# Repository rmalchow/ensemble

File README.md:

# ensemble has moved — it's now called Ondaire

This project was renamed. "Ensemble" is now **Ondaire**, self-hosted synchronized multiroom audio.

- New GitLab repo: https://gitlab.rand0m.me/share/ondaire
- New GitHub repo: https://github.com/rmalchow/ondaire

Please update your bookmarks, clones, and CI references — this repository is a placeholder only and receives no further updates.

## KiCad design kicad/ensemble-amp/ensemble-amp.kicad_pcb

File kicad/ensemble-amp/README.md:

# ensemble-amp — ESP32-S3 I2S Audio Amplifier

USB-C PD (20 V) → buck/LDO rails → ESP32-S3 → I2S → PCM5102A DAC → TPA3118D2 Class-D amp → stereo speakers.

**Single USB-C connector does everything**: PD negotiation runs on the CC wires while
USB 2.0 data (native ESP32-S3 USB, flashing/debug) runs on D+/D− — both at the same time.

Generated KiCad 10 project: schematic is **ERC-clean**, PCB has all footprints
**placed in functional blocks with full net assignment** — routing is left to you
(DRC shows only the expected unrouted ratsnest + silkscreen cosmetics).

## Architecture

```
USB-C ── CC1/CC2 ── HUSB238A PD sink (GPIO mode: 19.1k VSET=20V, 21k ISET=3A)
  │ VBUS ── SMAJ24A TVS ──── Q1 PMOS load switch (GATE-driven, soft start) ── VAMP rail (5…20V)
  │                                                                            ├─ TPA3118D2 PVCC/AVCC ── LC filters ── SPK L/R
  │                                                                            ├─ AP63205 buck → 5V ── AP2112K → 3.3V ── FB1 → 3V3A
  │                                                                            └─ 100k/10k divider → ESP32 ADC (IO7, rail monitor)
  └ D+/D− ── USBLC6 ESD ── ESP32-S3 native USB (flash/debug, works on any port)
ESP32-S3 ── I2S ── PCM5102A ── RC + AC coupling ── amp inputs
   └── I2C OLED · EC11 encoder · LEDs · UART header · amp control · PD_FAULT (IO14)
```

### How the PD negotiation behaves

The HUSB238A requests 20 V/3 A and walks the charger's PDO list from the top, taking the
first profile that satisfies ≥3 A — so the rail adapts to whatever you plug in:

| Charger | Rail (VAMP) | Approx. max audio power |
|---|---|---|
| 60 W+ PD | 20 V | ~2×25 W/8Ω, ~2×45 W/4Ω |
| 45 W PD | 15 V | ~2×14 W/8Ω, ~2×28 W/4Ω |
| 27–30 W PD | 9–12 V | ~2×5–9 W/8Ω |
| Plain USB port | 5 V | logic only — flashing/debug |

Firmware reads the actual rail through the 100k/10k divider on **IO7** (ADC1) — display
it on the OLED. **IO14 (PD_FAULT)** goes high if the charger can't cover the request or a
fault occurs. The amp's SDZ stays low until firmware decides the rail is adequate.

## Key design choices

- **USB-PD GPIO mode, not I2C**: in GPIO mode the HUSB238A's SDA/SCL pins permanently
  become the VSET/ISET analog straps, and sharing them with the ESP32 I2C bus would corrupt
  the strap reading at plug-in. Status is read via ADC + FAULT pin instead — robust, zero
  protocol risk. (ADDR/ORIENT floats = GPIO mode, per datasheet Table 6.)
- **Load switch**: HUSB238A GATE (open drain) drives the SUD45P03 PMOS; 100k gate pull-up,
  BZT52C10 zener clamps Vgs to −10 V (rail can be 20 V, FET Vgs(max) is ±20 V), 10 nF gives
  soft start. This matches the datasheet's GPIO-mode typical application (Fig. 4) one-to-one.
  Dead-battery attach is supported and the typical app has no other power path, so the
  switch closes at plain 5 V — the board boots when plugged into a computer. The chip's own
  OVP (120 % of requested voltage) opens the PMOS on overvoltage as a bonus protection layer.
  (Datasheet is marked *Preliminary*; GATE turn-on timing is an OTP option — verify on first
  article that VAMP comes up on a non-PD port.)
- **AP2112K-3.3 LDO** (250 mV dropout) instead of AMS1117 so the 3.3 V rail stays solid even
  in the 5 V-fallback case (buck output ≈4.7 V).
- **35 V bulk capacitors** (470 µF ×4) for the 20 V rail.
- **TPA3118D2 instead of TPA3116D2**: identical die and pinout (TI SLOS708G), but the
  thermal pad faces *down* — cooled by the PCB through the thermal-via array, no
  bolt-on heatsink. At 12 V both parts are supply-limited to the same output
  (~2×15 W @ 8 Ω, ~2×25 W @ 4 Ω). The amp symbol is in the project-local
  `ensemble.kicad_sym` library.
- **Gain**: 20 dB BTL master (R13 = 5.6 kΩ from GAIN/SLV to GND, datasheet Table).
  PCM5102A full scale is 2.1 Vrms → drives the amp to full 12 V output with margin.
- **MODSEL** tied low → classic BD modulation (matches the 10 µH + 680 nF output filter).
  AM0–AM2 low → default 400 kHz switching.
- **PLIMIT** tied to GVDD → no power limiting. Add a divider later if you want to cap output.
- **SDZ / MUTE** driven from GPIO through 100 kΩ series resistors (datasheet slew-rate
  requirement) with 100 kΩ pulldowns → amp stays off/un-muted-low until firmware says so.
- **PCM5102A** hardware-config mode: SCK grounded (internal PLL from BCK), FMT=I2S,
  FLT=normal, DEMP=off. XSMT has a 10 kΩ pulldown → DAC stays soft-muted until GPIO13 goes high.
- **Audio path**: OUT → 100 Ω + 2.2 nF RC (TPA3118 input sees clean HF) → 1 µF AC coupling →
  INP; INN AC-coupled to ground per channel (single-ended use of the differential input).
- **3V3A**: ferrite-isolated analog rail for PCM5102A AVDD/CPVDD.
- **USB data**: USBLC6 ESD protection on D+/D− (its VBUS clamp pin references the internal
  5 V rail, since connector VBUS may be 20 V). CC pulldowns are inside the HUSB238A.

## GPIO map (ESP32-S3)

| Function | GPIO | | Function | GPIO |
|---|---|---|---|---|
| I2S BCLK | IO15 | | Encoder A / B / SW | IO4 / IO5 / IO6 |
| I2S LRCK | IO16 | | Amp SDZ (high = on) | IO10 |
| I2S DOUT | IO17 | | Amp MUTE (high = mute) | IO11 |
| I2C SDA (OLED) | IO8 | | Amp FAULTZ (in, low = fault) | IO12 |
| I2C SCL (OLED) | IO9 | | DAC XSMT (high = unmute) | IO13 |
| Status LED 1 / 2 | IO47 / IO48 | | UART TX / RX (J3) | TXD0 / RXD0 |
| Spare on J3 | IO1, IO2 | | Boot / Reset buttons | IO0 / EN |
| VAMP sense (ADC1, 100k/10k) | IO7 | | PD fault (in, high = fault) | IO14 |

Power-up sequence in firmware: configure I2S → XSMT high → SDZ high → MUTE low.

## Routing guidance (the part left for you)

1. **Ground**: pour the B.Cu GND zone first (both zone outlines are already in the file,
   unfilled). Keep DAC/analog ground returns away from the amp's switching return paths.
2. **Amp**: PVCC decoupling (C36–C40) right at pins 18/19/31/32 with short, wide traces;
   bootstrap caps (C43–C46) directly at their pins; OUTx → L → film cap → terminal with
   ≥1.5 mm traces (AmpOutput net class is pre-set). Stitch the thermal-via pad to both GND planes.
3. **Buck**: keep the SW5V node (U1 pin SW → L1) tiny; input cap C4 hugging VIN/GND pins.
4. **USB**: route IO19/IO20 → USBLC6 → connector as a ~90 Ω differential pair (short here,
   so geometry is forgiving).
5. **Antenna**: the keep-out zone under the ESP32 antenna (both layers) is already placed —
   don't route or pour under it. Module antenna faces the bottom board edge.

## DRC notes (intentional)

- `unconnected_items`: the board ships unrouted by design.
- USB-C shield pads sit 0.15 mm from the board edge (connector overhangs); the project
  edge-clearance rule is set to 0.1 mm accordingly.
- Min through-hole is set to 0.2 mm for the ESP32 footprint's thermal vias.
- Silkscreen overlaps are cosmetic; nudge refdes during routing.

## Bring-up checklist

1. Populate the PD front end (U7, Q1 + gate parts, TVS) + buck/LDO. Plug into a plain USB
   port first: VAMP ≈ 5 V, +5 V/+3V3 up. Then a PD charger: VAMP should step to 20 V (or 15 V
   on a 45 W charger) about a second after attach.
2. Populate ESP32. Flash over USB-C (hold BOOT, tap RESET). Verify 3V3 ≥3.2 V during Wi-Fi TX.
3. Populate DAC; play I2S tone, scope OUTL/OUTR (2.1 Vrms max, 3 V DC bias before caps is normal **inside** the DAC — the outputs themselves are ground-centered).
4. Populate amp; SDZ low at first power, then enable with a small speaker / dummy load.

## Files

- `ensemble-amp.kicad_pro` / `.kicad_sch` / `.kicad_pcb` — open with KiCad ≥ 9
- `ensemble.kicad_sym` + `sym-lib-table` — project-local TPA3118D2 symbol
- `ensemble-amp-bom.csv` — grouped BOM (42 lines, ~85 components)
- `../generator/` — Python generators (single source of truth in `design.py` +
  `pcb_positions.py`; regenerate with `python3 gen_sch.py ../ensemble-amp/ensemble-amp.kicad_sch`
  and `python3 gen_pcb.py ../ensemble-amp/ensemble-amp.kicad_pcb`)

> ⚠ Generated design — review schematic and datasheet-critical values before ordering boards.

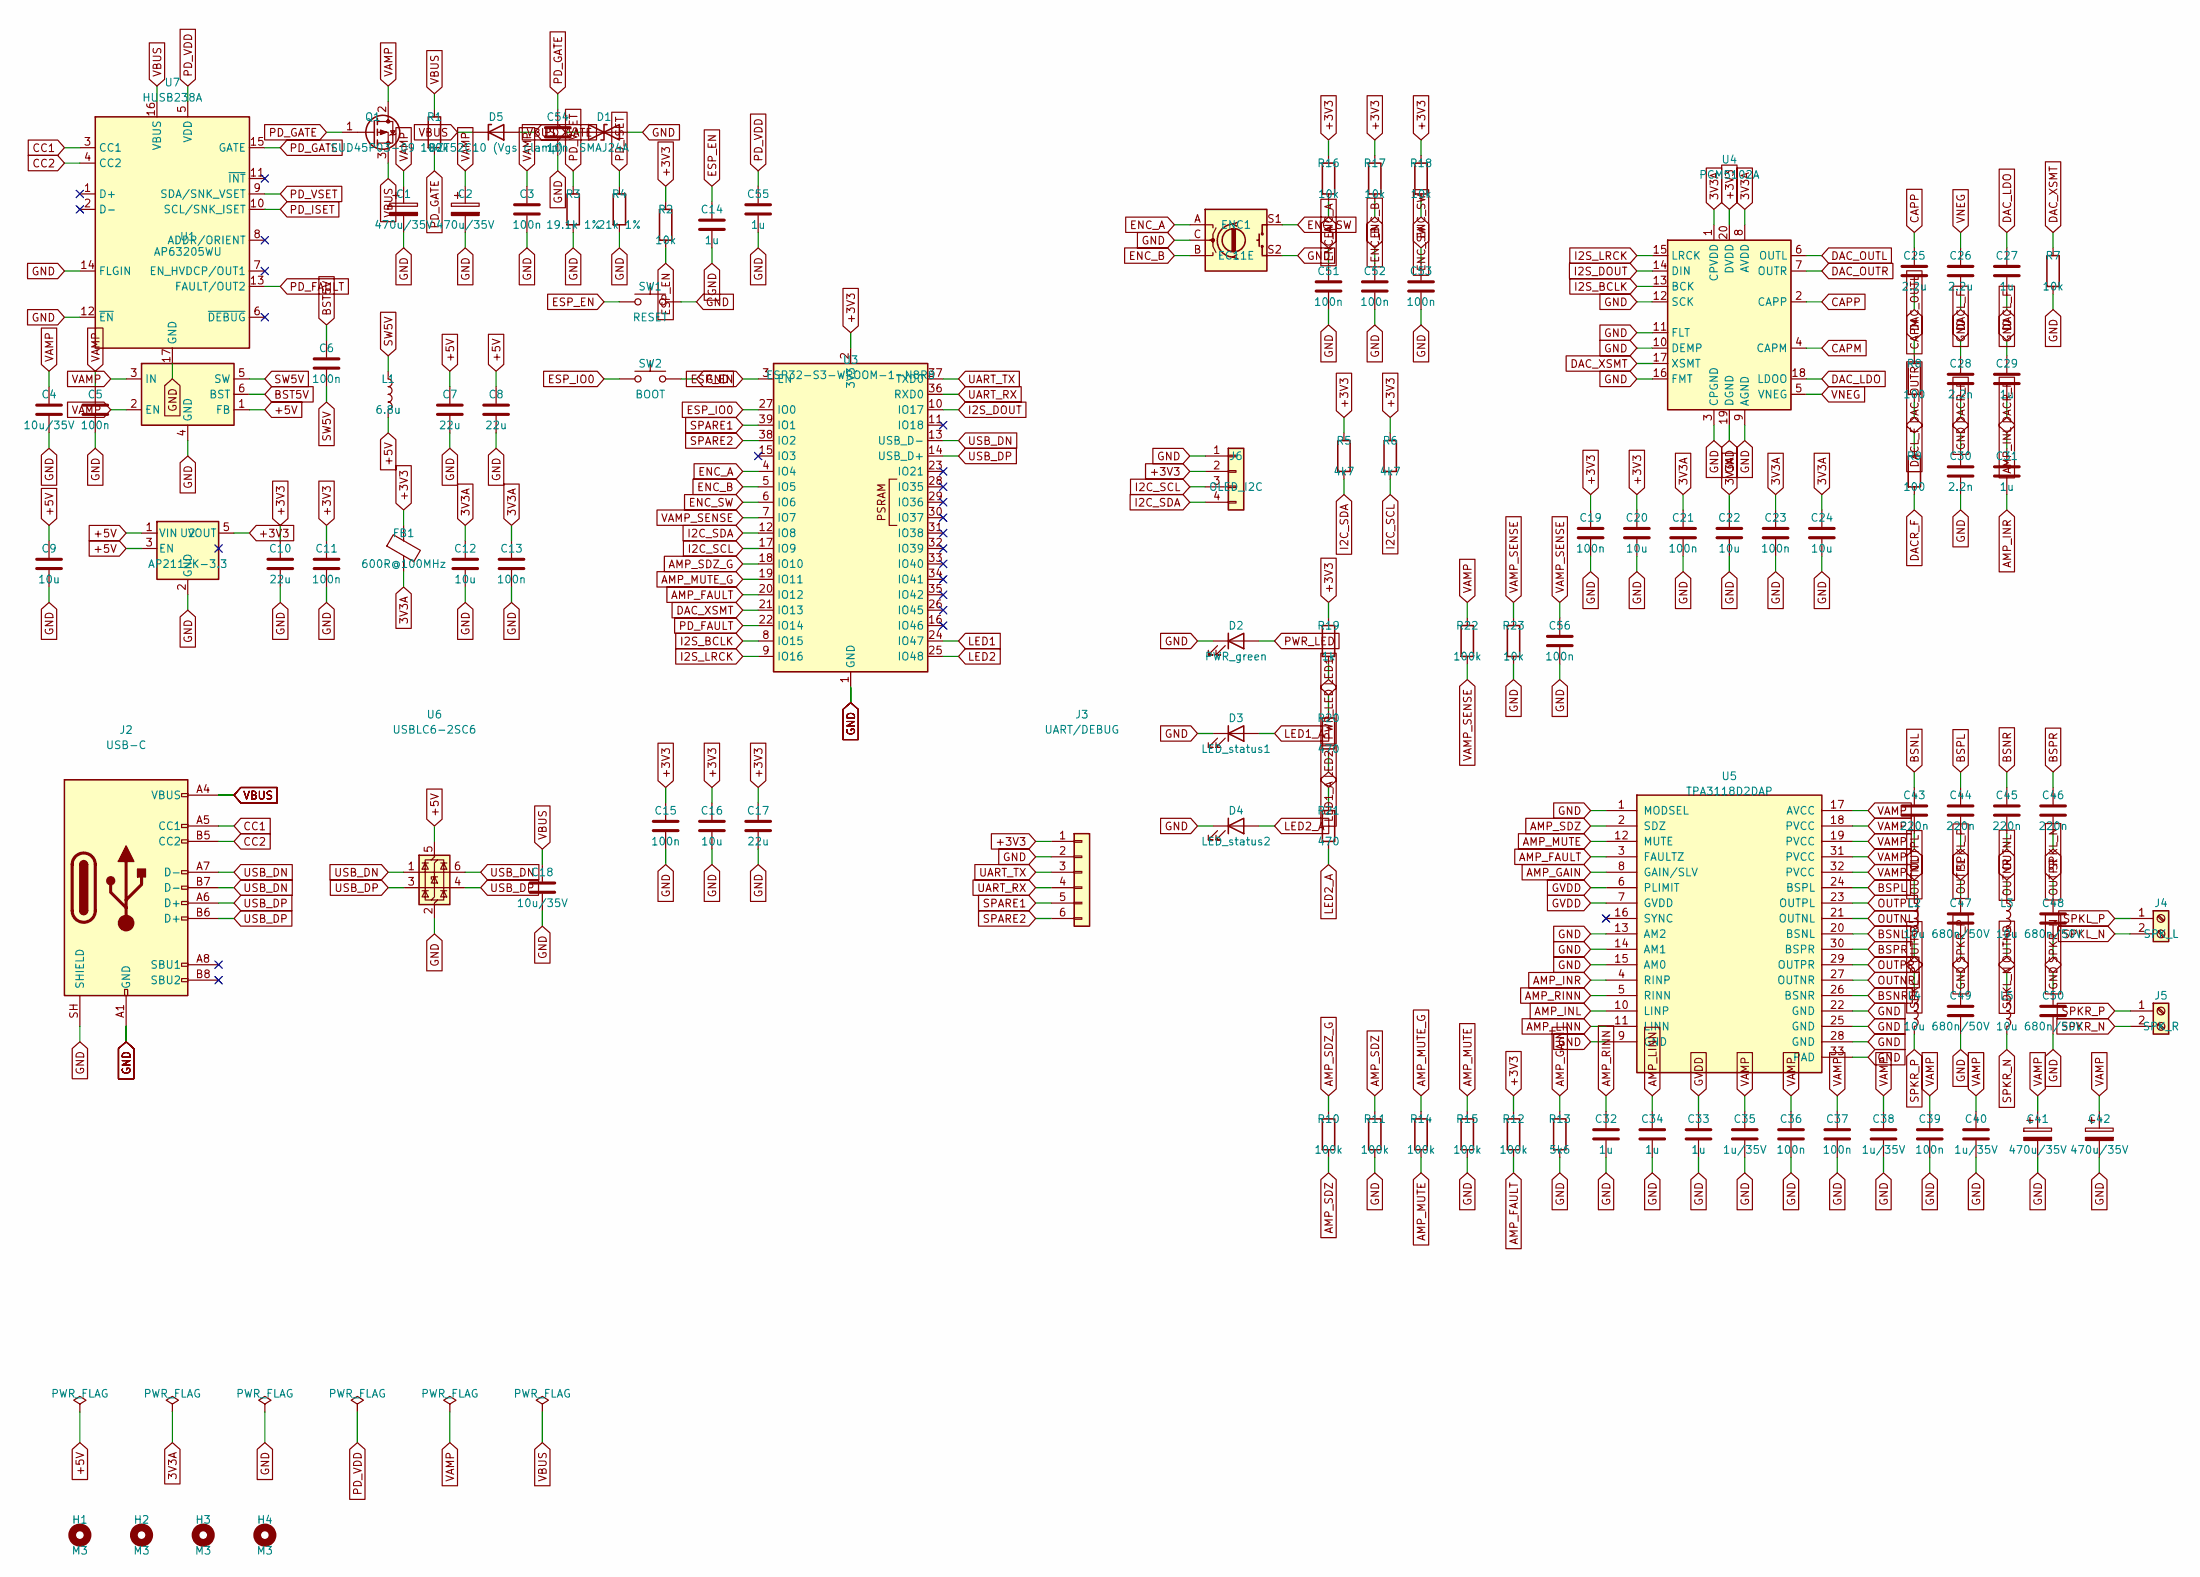
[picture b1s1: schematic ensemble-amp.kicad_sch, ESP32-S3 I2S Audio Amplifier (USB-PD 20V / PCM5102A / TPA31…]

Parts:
C1, C2, C41, C42: 470u/35V; CP_Radial_D12.5mm_P5.00mm
C3, C5, C6, C11, C13, C15, C19, C21, C23, C36, C37, C39, C51, C52, C53, C56: 100n; C_0603_1608Metric
C4, C18: 10u/35V; C_1210_3225Metric
C7, C8, C10, C17: 22u; C_0805_2012Metric
C9, C12, C16, C20, C22, C24: 10u; C_0805_2012Metric
C14, C27, C29, C31, C32, C33, C34, C55: 1u; C_0603_1608Metric
C25, C26: 2.2u; C_0805_2012Metric
C28, C30: 2.2n; C_0603_1608Metric
C35, C38, C40: 1u/35V; C_0603_1608Metric
C43, C44, C45, C46: 220n; C_0603_1608Metric
C47, C48, C49, C50: 680n/50V; C_1210_3225Metric
C54: 10n; C_0603_1608Metric
D1: SMAJ24A; D_SMA
D2: PWR_green; LED_0805_2012Metric
D3: LED_status1; LED_0805_2012Metric
D4: LED_status2; LED_0805_2012Metric
D5: BZT52C10 (Vgs clamp); D_SOD-123
ENC1: EC11E; RotaryEncoder_Alps_EC11E-Switch_Vertical_H20mm
FB1: 600R@100MHz; L_0805_2012Metric
H1, H2, H3, H4: M3; MountingHole_3.2mm_M3_DIN965
J2: USB-C; USB_C_Receptacle_HRO_TYPE-C-31-M-12
J3: UART/DEBUG; PinHeader_1x06_P2.54mm_Vertical
J4: SPK_L; TerminalBlock_Phoenix_MKDS-3-2-5.08_1x02_P5.08mm_Horizontal
J5: SPK_R; TerminalBlock_Phoenix_MKDS-3-2-5.08_1x02_P5.08mm_Horizontal
J6: OLED_I2C; PinHeader_1x04_P2.54mm_Vertical
L1: 6.8u; L_Coilcraft_XAL5030-XXX
L2, L3, L4, L5: 10u; L_12x12mm_H8mm
Q1: SUD45P03-09; TO-252-2
R1, R10, R11, R12, R14, R15, R22: 100k; R_0603_1608Metric
R2, R7, R16, R17, R18, R23: 10k; R_0603_1608Metric
R3: 19.1k 1%; R_0603_1608Metric
R4: 21k 1%; R_0603_1608Metric
R5, R6: 4k7; R_0603_1608Metric
R8, R9: 100; R_0603_1608Metric
R13: 5k6; R_0603_1608Metric
R19: 1k; R_0603_1608Metric
R20, R21: 470; R_0603_1608Metric
SW1: RESET; SW_SPST_B3S-1000
SW2: BOOT; SW_SPST_B3S-1000
U1: AP63205WU; TSOT-23-6
U2: AP2112K-3.3; SOT-23-5
U3: ESP32-S3-WROOM-1-N8R8; ESP32-S3-WROOM-1
U4: PCM5102A; TSSOP-20_4.4x6.5mm_P0.65mm
U5: TPA3118D2DAP; HTSSOP-32-1EP_6.1x11mm_P0.65mm_EP5.2x11mm_Mask4.11x4.36mm_T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
U6: USBLC6-2SC6; SOT-23-6
U7: HUSB238A; WQFN-16-1EP_3x3mm_P0.5mm_EP1.75x1.75mm

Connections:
3V3A: C12.1, C13.1, C21.1, C22.1, C23.1, C24.1, FB1.2, U4.1 (CPVDD), U4.8 (AVDD)
+3V3: C10.1, C11.1, C15.1, C16.1, C17.1, C19.1, C20.1, FB1.1, J3.1, J6.2, R2.1, R5.1, R6.1, R12.1, R16.1, R17.1, R18.1, R19.1, U2.5 (VOUT), U3.2 (3V3), U4.20 (DVDD)
+5V: C7.1, C8.1, C9.1, L1.2, U1.1 (FB), U2.1 (VIN), U2.3 (EN), U6.5 (VBUS)
AMP_FAULT: R12.2, U3.20 (IO12), U5.3 (FAULTZ)
AMP_GAIN: R13.1, U5.8 (GAIN/SLV)
AMP_INL: C29.2, U5.10 (LINP)
AMP_INR: C31.2, U5.4 (RINP)
AMP_LINN: C34.1, U5.11 (LINN)
AMP_MUTE: R14.2, R15.1, U5.12 (MUTE)
AMP_MUTE_G: R14.1, U3.19 (IO11)
AMP_RINN: C32.1, U5.5 (RINN)
AMP_SDZ: R10.2, R11.1, U5.2 (SDZ)
AMP_SDZ_G: R10.1, U3.18 (IO10)
BSNL: C43.1, U5.20 (BSNL)
BSNR: C45.1, U5.26 (BSNR)
BSPL: C44.1, U5.24 (BSPL)
BSPR: C46.1, U5.30 (BSPR)
BST5V: C6.1, U1.6 (BST)
CAPM: C25.2, U4.4 (CAPM)
CAPP: C25.1, U4.2 (CAPP)
CC1: J2.A5 (CC1), U7.3 (CC1)
CC2: J2.B5 (CC2), U7.4 (CC2)
DACL_F: C28.1, C29.1, R8.2
DACR_F: C30.1, C31.1, R9.2
DAC_LDO: C27.1, U4.18 (LDOO)
DAC_OUTL: R8.1, U4.6 (OUTL)
DAC_OUTR: R9.1, U4.7 (OUTR)
DAC_XSMT: R7.1, U3.21 (IO13), U4.17 (XSMT)
ENC_A: C51.1, ENC1.A, R16.2, U3.4 (IO4)
ENC_B: C52.1, ENC1.B, R17.2, U3.5 (IO5)
ENC_SW: C53.1, ENC1.S1, R18.2, U3.6 (IO6)
ESP_EN: C14.1, R2.2, SW1.1, U3.3 (EN)
ESP_IO0: SW2.1, U3.27 (IO0)
GND: C1.2, C2.2, C3.2, C4.2, C5.2, C7.2, C8.2, C9.2, C10.2, C11.2, C12.2, C13.2, C14.2, C15.2, C16.2, C17.2, C18.2, C19.2, C20.2, C21.2, C22.2, C23.2, C24.2, C26.2, C27.2, C28.2, C30.2, C32.2, C33.2, C34.2, C35.2, C36.2, C37.2, C38.2, C39.2, C40.2, C41.2, C42.2, C47.2, C48.2, C49.2, C50.2, C51.2, C52.2, C53.2, C54.2, C55.2, C56.2, D1.2 (A2), D2.1 (K), D3.1 (K), D4.1 (K), ENC1.C, ENC1.S2, J2.A1 (GND), J2.A12 (GND), J2.B1 (GND), J2.B12 (GND), J2.SH (SHIELD), J3.2, J6.1, R3.2, R4.2, R7.2, R11.2, R13.2, R15.2, R23.2, SW1.2, SW2.2, U1.4 (GND), U2.2 (GND), U3.1 (GND), U3.40 (GND), U3.41 (GND), U4.3 (CPGND), U4.9 (AGND), U4.10 (DEMP), U4.11 (FLT), U4.12 (SCK), U4.16 (FMT), U4.19 (DGND), U5.1 (MODSEL), U5.9 (GND), U5.13 (AM2), U5.14 (AM1), U5.15 (AM0), U5.22 (GND), U5.25 (GND), U5.28 (GND), U5.33 (PAD), U6.2 (GND), U7.12 (~EN), U7.14 (FLGIN), U7.17 (GND)
GVDD: C33.1, U5.6 (PLIMIT), U5.7 (GVDD)
I2C_SCL: J6.3, R6.2, U3.17 (IO9)
I2C_SDA: J6.4, R5.2, U3.12 (IO8)
I2S_BCLK: U3.8 (IO15), U4.13 (BCK)
I2S_DOUT: U3.10 (IO17), U4.14 (DIN)
I2S_LRCK: U3.9 (IO16), U4.15 (LRCK)
LED1: R20.1, U3.24 (IO47)
LED1_A: D3.2 (A), R20.2
LED2: R21.1, U3.25 (IO48)
LED2_A: D4.2 (A), R21.2
OUTNL: C43.2, L3.1, U5.21 (OUTNL)
OUTNR: C45.2, L5.1, U5.27 (OUTNR)
OUTPL: C44.2, L2.1, U5.23 (OUTPL)
OUTPR: C46.2, L4.1, U5.29 (OUTPR)
PD_FAULT: U3.22 (IO14), U7.13 (FAULT/OUT2)
PD_GATE: C54.1, D5.2 (A), Q1.1 (G), R1.2, U7.15 (GATE)
PD_ISET: R4.1, U7.10 (SCL/SNK_ISET)
PD_VDD: C55.1, U7.5 (VDD)
PD_VSET: R3.1, U7.9 (SDA/SNK_VSET)
PWR_LED: D2.2 (A), R19.2
SPARE1: J3.5, U3.39 (IO1)
SPARE2: J3.6, U3.38 (IO2)
SPKL_N: C48.1, J4.2, L3.2
SPKL_P: C47.1, J4.1, L2.2
SPKR_N: C50.1, J5.2, L5.2
SPKR_P: C49.1, J5.1, L4.2
SW5V: C6.2, L1.1, U1.5 (SW)
UART_RX: J3.4, U3.36 (RXD0)
UART_TX: J3.3, U3.37 (TXD0)
USB_DN: J2.A7 (D-), J2.B7 (D-), U3.13 (USB_D-), U6.1 (I/O1), U6.6 (I/O1)
USB_DP: J2.A6 (D+), J2.B6 (D+), U3.14 (USB_D+), U6.3 (I/O2), U6.4 (I/O2)
VAMP: C1.1, C2.1, C3.1, C4.1, C5.1, C35.1, C36.1, C37.1, C38.1, C39.1, C40.1, C41.1, C42.1, Q1.2 (D), R22.1, U1.2 (EN), U1.3 (IN), U5.17 (AVCC), U5.18 (PVCC), U5.19 (PVCC), U5.31 (PVCC), U5.32 (PVCC)
VAMP_SENSE: C56.1, R22.2, R23.1, U3.7 (IO7)
VBUS: C18.1, D1.1 (A1), D5.1 (K), J2.A4 (VBUS), J2.A9 (VBUS), J2.B4 (VBUS), J2.B9 (VBUS), Q1.3 (S), R1.1, U7.16 (VBUS)
VNEG: C26.1, U4.5 (VNEG)

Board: 2 copper layers, 110 parts (0 on the bottom side), 69 nets, no tracks yet.

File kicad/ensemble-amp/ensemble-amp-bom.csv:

"Reference","Value","Footprint"
"C1,C2,C41,C42","470u/35V","Capacitor_THT:CP_Radial_D12.5mm_P5.00mm"
"C3,C5,C6,C11,C13,C15,C19,C21,C23,C36,C37,C39,C51-C53,C56","100n","Capacitor_SMD:C_0603_1608Metric"
"C4,C18","10u/35V","Capacitor_SMD:C_1210_3225Metric"
"C7,C8,C10,C17","22u","Capacitor_SMD:C_0805_2012Metric"
"C9,C12,C16,C20,C22,C24,L2-L5","10u","Capacitor_SMD:C_0805_2012Metric,Inductor_SMD:L_12x12mm_H8mm"
"C14,C27,C29,C31-C34,C55","1u","Capacitor_SMD:C_0603_1608Metric"
"C25,C26","2.2u","Capacitor_SMD:C_0805_2012Metric"
"C28,C30","2.2n","Capacitor_SMD:C_0603_1608Metric"
"C35,C38,C40","1u/35V","Capacitor_SMD:C_0603_1608Metric"
"C43-C46","220n","Capacitor_SMD:C_0603_1608Metric"
"C47-C50","680n/50V","Capacitor_SMD:C_1210_3225Metric"
"C54","10n","Capacitor_SMD:C_0603_1608Metric"
"D1","SMAJ24A","Diode_SMD:D_SMA"
"D2","PWR_green","LED_SMD:LED_0805_2012Metric"
"D3","LED_status1","LED_SMD:LED_0805_2012Metric"
"D4","LED_status2","LED_SMD:LED_0805_2012Metric"
"D5","BZT52C10 (Vgs clamp)","Diode_SMD:D_SOD-123"
"ENC1","EC11E","Rotary_Encoder:RotaryEncoder_Alps_EC11E-Switch_Vertical_H20mm"
"FB1","600R@100MHz","Inductor_SMD:L_0805_2012Metric"
"H1-H4","M3","MountingHole:MountingHole_3.2mm_M3_DIN965"
"J2","USB-C","Connector_USB:USB_C_Receptacle_HRO_TYPE-C-31-M-12"
"J3","UART/DEBUG","Connector_PinHeader_2.54mm:PinHeader_1x06_P2.54mm_Vertical"
"J4","SPK_L","TerminalBlock_Phoenix:TerminalBlock_Phoenix_MKDS-3-2-5.08_1x02_P5.08mm_Horizontal"
"J5","SPK_R","TerminalBlock_Phoenix:TerminalBlock_Phoenix_MKDS-3-2-5.08_1x02_P5.08mm_Horizontal"
"J6","OLED_I2C","Connector_PinHeader_2.54mm:PinHeader_1x04_P2.54mm_Vertical"
"L1","6.8u","Inductor_SMD:L_Coilcraft_XAL5030-XXX"
"Q1","SUD45P03-09","Package_TO_SOT_SMD:TO-252-2"
"R1,R10-R12,R14,R15,R22","100k","Resistor_SMD:R_0603_1608Metric"
"R2,R7,R16-R18,R23","10k","Resistor_SMD:R_0603_1608Metric"
"R3","19.1k 1%","Resistor_SMD:R_0603_1608Metric"
"R4","21k 1%","Resistor_SMD:R_0603_1608Metric"
"R5,R6","4k7","Resistor_SMD:R_0603_1608Metric"
"R8,R9","100","Resistor_SMD:R_0603_1608Metric"
"R13","5k6","Resistor_SMD:R_0603_1608Metric"
"R19","1k","Resistor_SMD:R_0603_1608Metric"
"R20,R21","470","Resistor_SMD:R_0603_1608Metric"
"SW1","RESET","Button_Switch_SMD:SW_SPST_B3S-1000"
"SW2","BOOT","Button_Switch_SMD:SW_SPST_B3S-1000"
"U1","AP63205WU","Package_TO_SOT_SMD:TSOT-23-6"
"U2","AP2112K-3.3","Package_TO_SOT_SMD:SOT-23-5"
"U3","ESP32-S3-WROOM-1-N8R8","RF_Module:ESP32-S3-WROOM-1"
"U4","PCM5102A","Package_SO:TSSOP-20_4.4x6.5mm_P0.65mm"
"U5","TPA3118D2DAP","Package_SO:HTSSOP-32-1EP_6.1x11mm_P0.65mm_EP5.2x11mm_Mask4.11x4.36mm_ThermalVias"
"U6","USBLC6-2SC6","Package_TO_SOT_SMD:SOT-23-6"
"U7","HUSB238A","Package_DFN_QFN:WQFN-16-1EP_3x3mm_P0.5mm_EP1.75x1.75mm"

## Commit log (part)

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2026-06-06 first comit
2026-06-06 test: don't pin the exact post-genesis config version
    The role loop's background self-syncs (probed audio devices; the
    no-sink render fallback in CI containers) legitimately bump the doc
    version right after genesis, so 'version == 1 after restart' was a
    race. Assert what the test actually guards: the genesis content
    survives the restart (version >= 1, cluster name intact).
2026-06-06 fix: follower sync actually engages — gen gate, bounded drain; verbose diagnostics
    Two stacked bugs kept a follower's renderer permanently unsynced
    (render{sync=false want=0} while audio flowed uncontrolled):
    1. FollowerTimeline's streamGen gate was never set: it stayed 0 while
    chunks carried the live generation, so NowSample reported not-synced
    forever. The gate now seeds from the receiver's adopted generation
    and follows it across re-keys (play/stop/seek/failover).
2026-06-07 wipe: remove v1 implementation for ground-up rewrite
2026-06-07 docs: runtime library loading via purego — opus + alsa become v1, build tags abolished
    One universal binary, no cgo: libopus/libasound are dlopen'd at runtime
    (internal/dl probe helper, D32); capabilities are honest per-host runtime
    facts. Opus codec (master encodes once, members decode; member-capability
    validation, D33) and the alsa backend (exact DeviceDelay for the rate servo,
    D34) are both v1. Arch docs D/E/H/K patched; auto backend order alsa->exec->null.
2026-06-07 feat: wave 3 — group engine and HTTP API
    H: snapshot consumption + role classification, follow/unfollow validation,
    10s self-heal, MakeMaster orchestration, master play sessions (ticker,
    pts stamping via LocalToMaster+lead, opus encode, EOF vs live-stop,
    status+SourceStats heartbeat), member repoint (subscriber/clock/sink),
    live settings via gen bump; 57 tests -race green.
    I: Echo server with D19 status envelope, PATCH /api/node persist->replicate
2026-06-07 feat: group identity = master id; hybrid naming (derived labels + XOR-keyed overrides)
    D44: playback + settings records key by the MASTER's node id — membership
    churn (join/leave) can no longer orphan them, removing the D43 re-point
    patch by construction. Takeover copies settings to the new master's key
    (carry-over); playback stops as before; the group id now changes on
    takeover — what survives is the NAME.
    Naming is hybrid: server-side derived label from sorted member names
2026-06-07 feat: dumb-client spec + reference implementation; wire protocol v1 pinned
    docs/DUMB-CLIENT.md: self-contained implementer's spec for protocol-minimal
    audio clients (ESP32-class hardware): 24-byte header table, the seven
    packet types with mandatory/optional split, subscribe/clock/playout flows
    with the real timing constants, /api/cluster discovery subset, opus-on-WiFi
    guidance, conformance checklist.
    cmd/dumbclient: standalone reference client (~870 lines, stdlib only, zero
2026-06-07 feat: group settings editable in the UI and persisted with the master (D47)
    GroupCard: codec/transport selects + bufferMs slider (50-500, debounced),
    posting the full trio to the group's MASTER via the proxy; changes apply
    live (D23 RECONFIG). cluster.json now also persists the node's OWN
    group-settings record (full version+writer for LWW; D7-style restart
    version reconcile) — a master restart keeps its group's codec/transport/
    buffer instead of resetting to defaults.
2026-06-07 fix: revert device-queue deadline coupling (choppy feedback loop); alsa latency fixed at 60ms
    User-reported regression: playback turned really choppy after 3e30b85.
    Subtracting the live device queue from deadlines is an unstable feedback
    loop — earlier writes fill the queue, growing the measurement, moving
    deadlines earlier still, until the jitter buffer oscillates between burst
    and starvation. Reverted.
    The original ~180ms phase offset is fixed at its SOURCE instead: the alsa
2026-06-08 fix: volume-slider PATCH flood; e2e fixture length + CI e2e non-blocking
    Volume flood: a dragging volume slider sent hundreds of identical PATCHes
    (user saw a wall of "gain changed volume=0.8"). Guards at every layer now:
    the slider de-dupes (never re-sends the same value), sink.SetGain no-ops +
    no-logs when the target is unchanged, and cluster.SetVolume already no-op'd
    when unchanged (no broadcast → no WS echo loop).
    CI e2e: the job failed at step 11 because the 12s tone fixture hit natural
2026-06-08 docs: root README — overview, quick start, UI guide
2026-06-08 ui: roomier advanced settings (2-col grid) + calibration mic selector
    Advanced settings were crammed onto one wrapping line; lay them out as a
    two-column label|control grid, one setting per row, with a full-width buffer
    slider. Add a 'Calibration' row with a microphone selector listing the group
    members that expose an input/line-in capability (the calibration recorder
    must be a clock-synced member). Calibrate button stays a placeholder until the
    calibration API lands; the mic selection is wired and ready for it.
2026-06-08 calibrate: wire end-to-end — calibrate: source, REST API, UI button
    Backend:
    - internal/audio/calibrate_src.go: 'calibrate:' source scheme looping the
    windowed sweep forever (live-paced); master streams it via group.Play. Signal
    is the same calibrate.NewReference(default) the estimator correlates against.
    - internal/api/calibrate.go: POST/GET /api/calibrate on the mic node. Controller
    drives /api/play|stop on the master and PATCH /api/node volume/delay on each
2026-06-08 calibrate: record via continuous raw capture (real root cause of 0 confidence)
    The recorder used the live input: Source, whose liveReader inserts a SILENCE
    frame whenever a frame isn't ready within one frame period. That is correct for
    the real-time-paced playback pull, but the calibration recorder drains faster
    than real time, so it hit the deadline constantly: on-hardware ~169/350 captured
    frames were silence, shredding the sweep → EstimateDelay found no peak →
    confidence 0 for every node ('no confident measurements').
2026-06-09 v0.2.0: remove calibration, redesign room cards, inline media, Spotify bridge
    Acoustic auto-calibration (D48) removed — internal/calibrate, the calibrate:
    source + /api/calibrate, and the group-card wizard are gone (−2.4k lines).
    Per-node delay is still tunable by hand (D36); cross-room sync is D65.
    Room-card redesign (Rams reviews):
    - Headline is now "[master]: [players]" (or italic "no players"); group/member
    renaming moved off the cards (node names are edited on the Nodes page).
2026-06-10 test: deflake TestPlayoutSetGainHalves under CI starvation
    The playout is real-time-paced (wall-clock fakeClock), so a loaded/slow CI
    runner deschedules the scheduler past a frame's deadline and that frame is
    late-dropped (sink.go:517) — leaving Played=7 of 8 and failing the strict
    `Played >= 8` wait.
    The gain ramp settles within one frame, so the assertion only needs the last
    WRITTEN frame to be settled. Wait until all 8 frames are PROCESSED (played OR
2026-06-10 feat(metadata): now-playing source metadata channel (D57)
    Add an optional metadata channel so the UI's now-playing box can show track
    title/artist/album/cover art:
    - contracts: TrackMetadata + Playback.Metadata (omitempty).
    - spotify bridge: parse album_name/album_cover_url/duration from go-librespot
    metadata events; store latest under mutex; Latest() accessor + OnMetadata hook.
    Also add SetDeviceName() (POST /set_device_name) for live Connect renames.
2026-06-10 fix(ui): endpoint rename/toggle re-render (immutable $state updates)
    In-place mutation of a $state array element (endpoints[i].name = ...) updated
    the data + backend but left the keyed {#each} item's EditableText showing the
    stale value. Reassign the array immutably so the row re-renders.
2026-06-10 fix(spotify): include the master's own player in a preset group
    setGroupMembers only joined non-gossiping playback nodes (AssignPlaybackNode),
    so when the master node itself was one of a preset's players its own speaker was
    never (re)added on play — the other (playback) nodes joined reliably, the master
    didn't. The master is a gossiping node: it joins by following itself. On play,
    Follow(self) when the master is a wanted player, Unfollow() when it isn't (and is
    currently in its own group; a crosswise follow is left alone).
2026-06-10 fix(spotify): capture track metadata from the "playing" event (go-librespot 0.7.3)
    go-librespot 0.7.3 carries the track name/artist on the "playing" event, not (or
    not only) a dedicated "metadata" event — so capturing metadata only in the
    "metadata" case left b.meta empty and the now-playing bar fell back to "Spotify".
    Capture metadata from ANY event that carries a name (playing or metadata).
2026-06-10 feat(ui): spotify presence badge on the Nodes page
    Nodes that run go-librespot (caps.sources includes spotify) get a non-toggle
    'spotify' badge (Spotify green) in the features row.
2026-06-10 fix(ui): use a near-display-size wordmark (crisp); keep full-size master
    The full-size wordmark.png (1884x528) downscaled to 22px muddied the serifs.
    Add wordmark-small.png rendered near display size and use that in the header;
    keep the big one in the repo (unreferenced) for future high-res use.
2026-06-10 feat: gapless file-source play queue with MP3 tags
    Add a real play queue to the file source, streamed gaplessly and surfaced
    in the UI.
    - queueSource (internal/group): chains queued files within ONE session, so
    the generation never changes and the stream is continuous across tracks;
    outer EOF only when the queue drains. PlayNow/Append/Next/RemoveUpcoming +
    per-track Now() progress.
2026-06-11 feat(ui+sink): queue play-now, on-demand queue, transport bar, sink self-heal
    - feat(queue): click an upcoming track to play it now (atomic promote:
    queueSource.PlayUpcoming → Engine.PlayQueuedNow → POST /queue/play).
    - fix(cluster): stop gossiping queue items — a big queue blew memberlist's UDP
    packet so the playback record fell back to the 30s push/pull, delaying players.
    Now only queueLen + a queueRev change marker ride the record; the UI pulls the
    items live from the master via GET /queue (proxied). Fixes slow propagation on
2026-06-11 fix(spotify): drive now-playing position from go-librespot, not wall-clock
    The master timed Spotify position as wall-clock elapsed since the stream
    started (now - startedUnix), so a phone-side seek/replay never reached the
    playback record — the UI clock saw no discontinuity and kept climbing past
    the real position.
    Capture the position go-librespot reports on its metadata + seek events and
    free-run it at 1x (frozen while paused), exposed via a new PositionSource
2026-06-11 fix(arm): ship hard-float armv6hf build for Raspberry Pi OS
    The 32-bit binary failed on Raspberry Pi OS with "cannot execute:
    required file not found". purego forces dynamic linking on linux/arm
    even at CGO_ENABLED=0, and Go stamps the soft-float armel loader
    /lib/ld-linux.so.3 — absent on hard-float armhf userlands like
    Raspberry Pi OS, which only ship /lib/ld-linux-armhf.so.3.
    Ship both 32-bit variants from the same GOARM=6 code, differing only
